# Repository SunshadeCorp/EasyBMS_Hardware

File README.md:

# EasyBMS_Hardware
PCB of the EasyBMS as an EAGLE project

Used EAGLE default design rules with one modification: under "Masks" in DRC settings, set "Limit" to 20mil to cover vias that have smaller drill size with solder mask.

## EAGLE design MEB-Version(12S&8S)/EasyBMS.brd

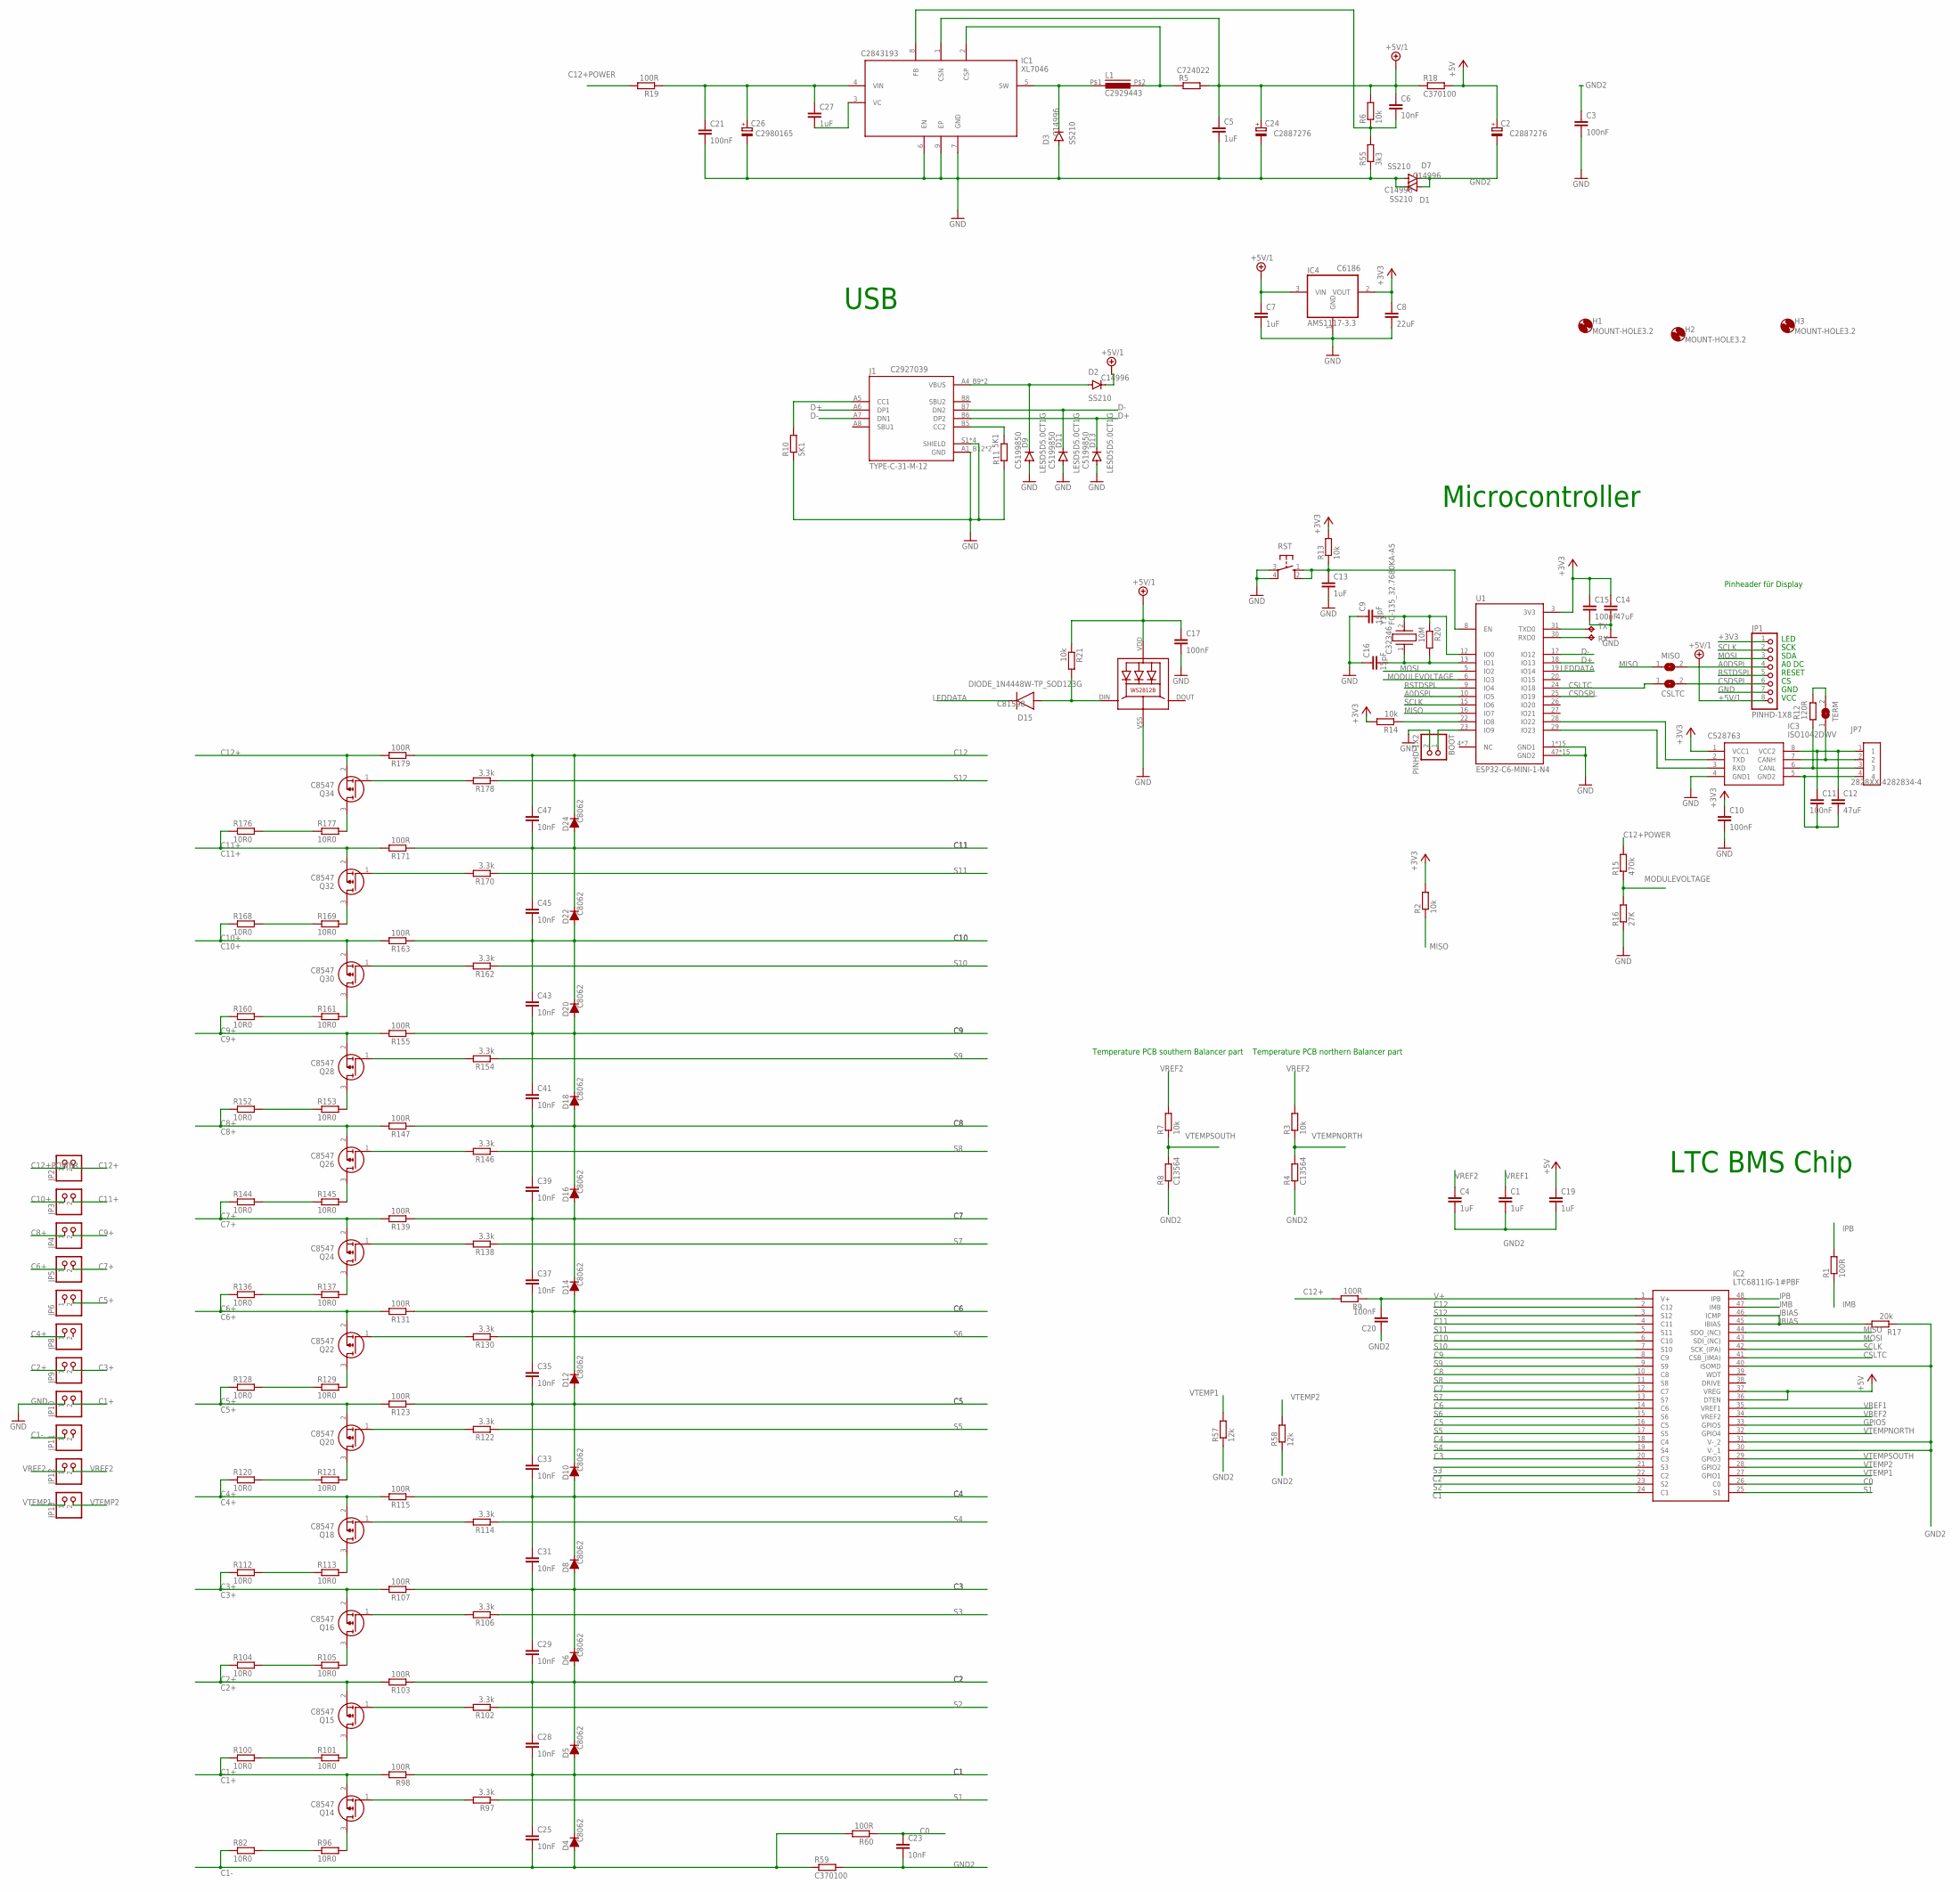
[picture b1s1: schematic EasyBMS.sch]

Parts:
BOOT: PINHD-1X2; 1X02
C1, C4, C5, C7, C13, C19: 1uF; C0402
C2, C24: CPOL-EU153CLV-0605; 153CLV-0605; LCSC C2887276
C3, C10, C11, C15, C17: 100nF; C0402
C6, C23, C25, C28, C29, C31, C33, C35, C37, C39, C41, C43, C45, C47: 10nF; C0402
C8: 22uF; C0603
C9, C16: 15pF; C0402
C12: 47uF; C1206
C14: 47uF; C0805
C20, C21: 100nF; C0805
C26: CPOL-EU153CLV-0605; 153CLV-0605; LCSC C2980165
C27: 1uF; C0603
CSLTC: SJ
D1, D2, D3, D7: SS210; DO214AC; LCSC C14996
D4, D5, D6, D8, D10, D12, D14, D16, D18, D20, D22, D24: D-FILL-MLL-34; MELF-MLL34; LCSC C8062
D9, D11, D13: LESD5D5.0CT1G; SOD523; LCSC C5199850
D15: DIODE_1N4448W-TP_SOD123G; SOD3715X135; LCSC C81598
H1, H2, H3: MOUNT-HOLE3.2; 3,2
IC1: XL7046; SOIC127P600X170-9N; LCSC C2843193
IC2: LTC6811IG-1#PBF; SOP50P780X200-48N
IC3: ISO1042DWV; SOIC127P1150X280-8N; LCSC C528763
IC4: AMS1117-3.3; SOT223; LCSC C6186
J1: TYPE-C-31-M-12; HRO_TYPE-C-31-M-12; LCSC C2927039
JP1: PINHD-1X8; 1X08
JP2, JP3, JP4, JP5, JP6, JP8, JP9, JP10, JP11, JP12, JP13: PINHD-1X2; 1X02; LCSC C3337950
JP7: 2828XX-4282834-4; TERMBLK_254-4N
L1: C2929443; CY75-100UH; LCSC C2929443
LED2: XL-1615RGBC-WS2812B
MISO: SJ
Q14, Q15, Q16, Q18, Q20, Q22, Q24, Q26, Q28, Q30, Q32, Q34: C8547; PG-SOT-23
R1: 100R; R0603
R2, R6, R13, R14, R21: 10k; R0402
R3, R7: 10k; R0603
R4, R8: C13564; R0603
R5: R-EU_R0402; R0402; LCSC C724022
R9, R60, R98, R103, R107, R115, R123, R131, R139, R147, R155, R163, R171, R179: 100R; R0402
R10, R11: 5K1; R0402
R12: 120R; R0402
R15: 470k; R0603
R16: 27K; R0603
R17: 20k; R0603
R18, R59: C370100; R1206
R19: 100R; R1206
R20: 10M; R0402
R55: 3k3; R0402
R57, R58: 12k; R0402
R82, R96, R100, R101, R104, R105, R112, R113, R120, R121, R128, R129, R136, R137, R144, R145, R152, R153, R160, R161, R168, R169, R176, R177: 10R0; R1206
R97, R102, R106, R114, R122, R130, R138, R146, R154, R162, R170, R178: 3.3k; R0402
RST: 10-XX; B3F-10XX
RX: TPB2,54; B2,54
TERM: SJ
TX: TPB2,54; B2,54
U1: ESP32-C6-MINI-1-N4; XCVR_ESP32-C6-MINI-1-N4; LCSC C5736265
Y1: FC-135_32.7680KA-A5; FC135327680KAA5; LCSC C32346

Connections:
+3V3: C8.1, C10.1, C14.1, C15.1, IC3.1 (VCC1), IC4.2 (VOUT), JP1.1, R2.2, R13.2, R14.2, U1.3 (3V3)
+5V: C2.+, C19.1, IC2.36 (DTEN), IC2.37 (VREG), R18.2
+5V/1: C5.1, C6.1, C7.1, C17.1, C24.+, D2.C, IC1.1 (CSN), IC4.3 (VIN), JP1.8, LED2.VDD, R5.2, R6.2, R18.1, R21.1
A0DSPL: JP1.4, MISO.2, U1.10 (IO5)
C0: C23.1, IC2.26 (C0), R60.1
C1: C25.1, C28.2, D4.1 (C), D5.2 (A), IC2.24 (C1), R98.1
C1+: JP10.2, Q14.2 (S), R98.2, R100.1
C1-: C25.2, D4.2 (A), JP11.1, R59.1, R60.2, R82.1
C2: C28.1, C29.2, D5.1 (C), D6.2 (A), IC2.22 (C2), R103.1
C2+: JP9.1, Q15.2 (S), R103.2, R104.1
C3: C29.1, C31.2, D6.1 (C), D8.2 (A), IC2.20 (C3), R107.1
C3+: JP9.2, Q16.2 (S), R107.2, R112.1
C4: C31.1, C33.2, D8.1 (C), D10.2 (A), IC2.18 (C4), R115.1
C4+: JP8.1, Q18.2 (S), R115.2, R120.1
C5: C33.1, C35.2, D10.1 (C), D12.2 (A), IC2.16 (C5), R123.1
C5+: JP6.2, Q20.2 (S), R123.2, R128.1
C6: C35.1, C37.2, D12.1 (C), D14.2 (A), IC2.14 (C6), R131.1
C6+: JP5.1, Q22.2 (S), R131.2, R136.1
C7: C37.1, C39.2, D14.1 (C), D16.2 (A), IC2.12 (C7), R139.1
C7+: JP5.2, Q24.2 (S), R139.2, R144.1
C8: C39.1, C41.2, D16.1 (C), D18.2 (A), IC2.10 (C8), R147.1
C8+: JP4.1, Q26.2 (S), R147.2, R152.1
C9: C41.1, C43.2, D18.1 (C), D20.2 (A), IC2.8 (C9), R155.1
C9+: JP4.2, Q28.2 (S), R155.2, R160.1
C10: C43.1, C45.2, D20.1 (C), D22.2 (A), IC2.6 (C10), R163.1
C10+: JP3.1, Q30.2 (S), R163.2, R168.1
C11: C45.1, C47.2, D22.1 (C), D24.2 (A), IC2.4 (C11), R171.1
C11+: JP3.2, Q32.2 (S), R171.2, R176.1
C12: C47.1, D24.1 (C), IC2.2 (C12), R179.1
C12+: JP2.2, Q34.2 (S), R9.2, R179.2
C12+POWER: JP2.1, R15.2, R19.2
CSDSPL: CSLTC.2, JP1.6, U1.25 (IO19)
CSLTC: CSLTC.1, IC2.41 (CSB_(IMA)), U1.24 (IO18)
D+: D13.C, J1.A6 (DP1), J1.B6 (DP2), U1.18 (IO13)
D-: D11.C, J1.A7 (DN1), J1.B7 (DN2), U1.17 (IO12)
GND: BOOT.2, C3.2, C5.2, C7.2, C8.2, C9.1, C10.2, C13.2, C14.2, C15.2, C16.1, C17.2, C21.2, C24.-, C26.-, D1.C, D3.A, D7.A, D9.A, D11.A, D13.A, IC1.6 (EN), IC1.7 (GND), IC1.9 (EP), IC3.4 (GND1), IC4.1 (GND), J1.A1_B12 (GND), J1.B1_A12 (GND), J1.S1 (SHIELD), J1.S2 (SHIELD), J1.S3 (SHIELD), J1.S4 (SHIELD), JP1.7, JP10.1, LED2.VSS (GND), R10.1, R11.1, R16.1, R55.1, RST.3, RST.4 (P1), U1.1 (GND1), U1.2 (GND1), U1.11 (GND1), U1.14 (GND1), U1.36 (GND1), U1.37 (GND1), U1.38 (GND1), U1.39 (GND1), U1.40 (GND1), U1.41 (GND1), U1.42 (GND1), U1.43 (GND1), U1.44 (GND1), U1.45 (GND1), U1.46 (GND1), U1.47 (GND2), U1.48 (GND2), U1.49_1 (GND2), U1.49_2 (GND2), U1.49_3 (GND2), U1.49_4 (GND2), U1.49_5 (GND2), U1.49_6 (GND2), U1.49_7 (GND2), U1.49_8 (GND2), U1.49_9 (GND2), U1.50 (GND2), U1.51 (GND2), U1.52 (GND2), U1.53 (GND2)
GND2: C1.2, C2.-, C3.1, C4.2, C19.2, C20.1, C23.2, D1.A, D7.C, IC2.30 (V-_1), IC2.31 (V-_2), IC2.40 (ISOMD), R4.1, R8.1, R17.1, R57.1, R58.1, R59.2
GPIO5: IC2.33 (GPIO5)
IBIAS: IC2.45 (IBIAS), IC2.46 (ICMP), R17.2
IMB: IC2.47 (IMB), R1.1
IPB: IC2.48 (IPB), R1.2
LEDDATA: D15.1 (C), U1.19 (IO14)
MISO: IC2.44 (SDO_(NC)), MISO.1, R2.1, U1.16 (IO7)
MODULEVOLTAGE: R15.1, R16.2, U1.6 (IO3)
MOSI: IC2.43 (SDI_(NC)), JP1.3, U1.5 (IO2)
unnamed: IC3.2 (TXD), U1.28 (IO22)
unnamed: TX.TP, U1.31 (TXD0)
unnamed: D2.A, D9.C, J1.A4_B9 (VBUS), J1.B4_A9 (VBUS)
unnamed: C27.2, IC1.3 (VC)
unnamed: D3.C, IC1.5 (SW), L1.P$1 (1)
unnamed: J1.A5 (CC1), R10.2
unnamed: J1.B5 (CC2), R11.2
unnamed: RX.TP, U1.30 (RXD0)
unnamed: IC3.3 (RXD), U1.29 (IO23)
unnamed: C11.1, C12.1, IC3.8 (VCC2), JP7.1
unnamed: IC3.7 (CANH), JP7.2, TERM.1
unnamed: IC3.6 (CANL), JP7.3, R12.1
unnamed: IC1.2 (CSP), L1.P$2 (2), R5.1
unnamed: C11.2, C12.2, IC3.5 (GND2), JP7.4
unnamed: C13.1, R13.1, RST.1 (S), RST.2 (S1), U1.8 (EN)
unnamed: R82.2, R96.1
unnamed: R12.2, TERM.2
unnamed: R14.1, U1.22 (IO8)
unnamed: BOOT.1, U1.23 (IO9)
unnamed: C9.2, R20.1, U1.12 (IO0), Y1.2
unnamed: C16.2, R20.2, U1.13 (IO1), Y1.1
unnamed: D15.2 (A), LED2.DIN (DI), R21.2
unnamed: C6.2, IC1.8 (FB), R6.1, R55.2
unnamed: C21.1, C26.+, C27.1, IC1.4 (VIN), R19.1
unnamed: Q14.3 (D), R96.2
unnamed: Q14.1 (G), R97.2
unnamed: R100.2, R101.1
unnamed: Q15.3 (D), R101.2
unnamed: Q15.1 (G), R102.2
unnamed: R104.2, R105.1
unnamed: Q16.3 (D), R105.2
unnamed: Q16.1 (G), R106.2
unnamed: R112.2, R113.1
unnamed: Q18.3 (D), R113.2
unnamed: Q18.1 (G), R114.2
unnamed: R120.2, R121.1
unnamed: Q20.3 (D), R121.2
unnamed: Q20.1 (G), R122.2
unnamed: R128.2, R129.1
unnamed: Q22.3 (D), R129.2
unnamed: Q22.1 (G), R130.2
unnamed: R136.2, R137.1
unnamed: Q24.3 (D), R137.2
unnamed: Q24.1 (G), R138.2
unnamed: R144.2, R145.1
unnamed: Q26.3 (D), R145.2
unnamed: Q26.1 (G), R146.2
unnamed: R152.2, R153.1
unnamed: Q28.3 (D), R153.2
unnamed: Q28.1 (G), R154.2
unnamed: R160.2, R161.1
unnamed: Q30.3 (D), R161.2
unnamed: Q30.1 (G), R162.2
unnamed: R168.2, R169.1
unnamed: Q32.3 (D), R169.2
unnamed: Q32.1 (G), R170.2
unnamed: R176.2, R177.1
unnamed: Q34.3 (D), R177.2
unnamed: Q34.1 (G), R178.2
RSTDSPL: JP1.5, U1.9 (IO4)
S1: IC2.25 (S1), R97.1
S2: IC2.23 (S2), R102.1
S3: IC2.21 (S3), R106.1
S4: IC2.19 (S4), R114.1
S5: IC2.17 (S5), R122.1
S6: IC2.15 (S6), R130.1
S7: IC2.13 (S7), R138.1
S8: IC2.11 (S8), R146.1
S9: IC2.9 (S9), R154.1
S10: IC2.7 (S10), R162.1
S11: IC2.5 (S11), R170.1
S12: IC2.3 (S12), R178.1
SCLK: IC2.42 (SCK_(IPA)), JP1.2, U1.15 (IO6)
V+: C20.2, IC2.1 (V+), R9.1
VREF1: C1.1, IC2.35 (VREF1)
VREF2: C4.1, IC2.34 (VREF2), JP12.1, JP12.2, R3.2, R7.2
VTEMP1: IC2.27 (GPIO1), JP13.1, R57.2
VTEMP2: IC2.28 (GPIO2), JP13.2, R58.2
VTEMPNORTH: IC2.32 (GPIO4), R3.1, R4.2
VTEMPSOUTH: IC2.29 (GPIO3), R7.1, R8.2

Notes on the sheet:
LED
SCK
SDA
A0 DC
RESET
GND
VCC
Pinheader für Display
Microcontroller
LTC BMS Chip
Temperature PCB northern Balancer part
Temperature PCB southern Balancer part
USB

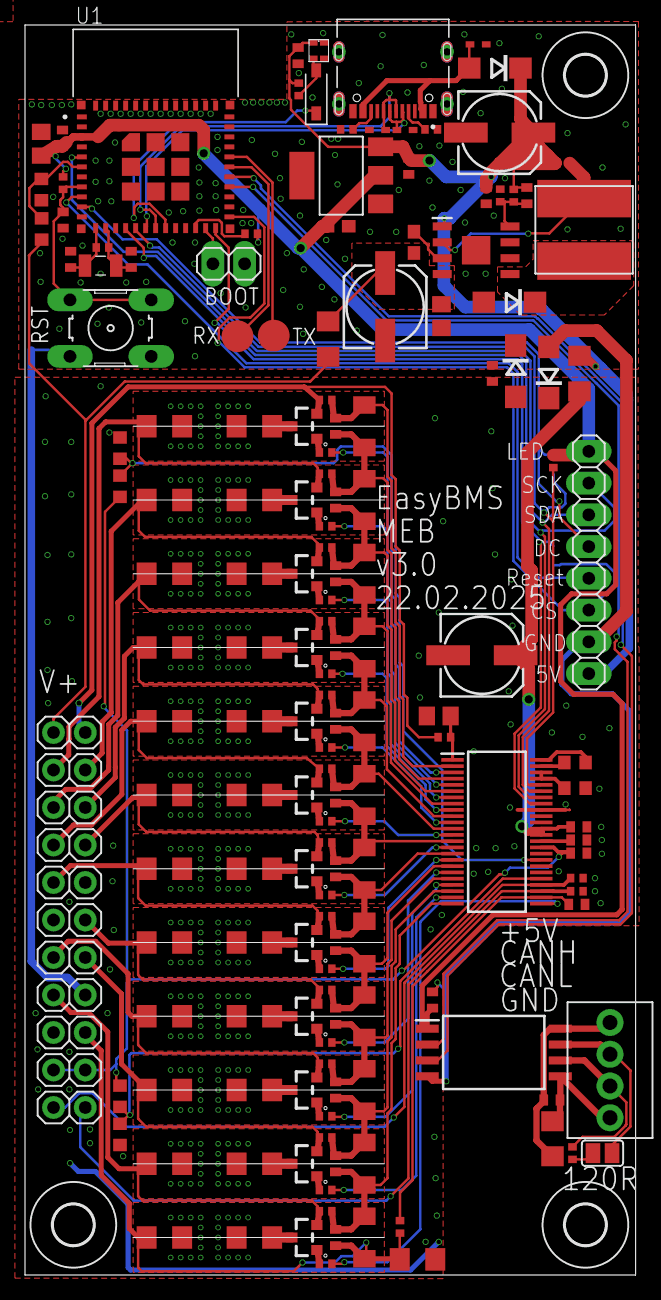
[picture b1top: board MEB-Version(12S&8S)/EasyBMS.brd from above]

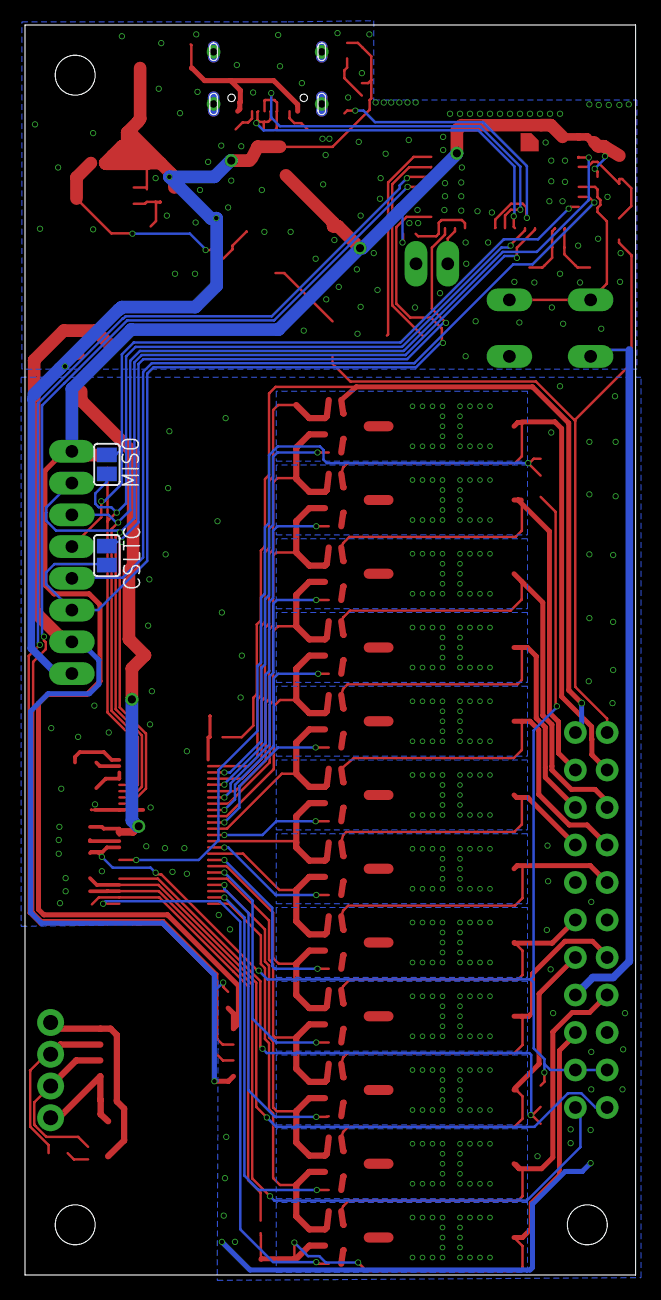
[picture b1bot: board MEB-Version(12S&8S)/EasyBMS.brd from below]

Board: 2 copper layers, 48.9 x 100.0 mm, 174 parts (2 on the bottom side), 124 nets.

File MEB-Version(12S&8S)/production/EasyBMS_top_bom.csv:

Comment,Designator,Footprint,LCSC Part #
1uF,C2 C24 C26 D4 D5 D6 D8 D10 D12 D14 D16 D18 D20 D22 D24 R5 TERM C1 C4 C5 C7 C13 C19,C0402,
1uF,C27,C0603,
3.3k,R97 R102 R106 R114 R122 R130 R138 R146 R154 R162 R170 R178,R0402,
3k3,R55,R0402,
5K1,R10 R11,R0402,
10M,R20,R0402,
10R0,R82 R96 R100 R101 R104 R105 R112 R113 R120 R121 R128 R129 R136 R137 R144 R145 R152 R153 R160 R161 R168 R169 R176 R177,R1206,
10k,R2,R0402,
10k,R3,R0603,
10k,R6,R0402,
10k,R7,R0603,
10k,R13 R14 R21,R0402,
10nF,C6 C23 C25 C28 C29 C31 C33 C35 C37 C39 C41 C43 C45 C47,C0402,
12k,R57 R58,R0402,
15pF,C9 C16,C0402,
20k,R17,R0603,
22uF,C8,C0603,
27K,R16,R0402,
47µF,C12,C1206,
47µF,C14,C0805,
100R,R1,R0603,
100R,R9,R0402,
100R,R19,R1206,
100R,R60 R98 R103 R107 R115 R123 R131 R139 R147 R155 R163 R171 R179,R0402,
100nF,C3 C10 C11 C15 C17,C0402,
100nF,C20 C21,C0805,
120R,R12,R0402,
470k,R15,R0402,
AMS1117-3.3,IC4,SOT223,C6186
C8547,Q14 Q15 Q16 Q18 Q20 Q22 Q24 Q26 Q28 Q30 Q32 Q34,PG-SOT-23,
C13564,R4 R8,R0603,
C370100,R18 R59,R1206,
C2929443,L1,CY75-100UH,C2929443
DIODE_1N4448W-TP_SOD123G,D15,SOD3715X135,C81598
ESP32-C6-MINI-1-N4,U1,XCVR_ESP32-C6-MINI-1-N4,C5736265
FC-135_32.7680KA-A5,Y1,FC135327680KAA5,C32346
ISO1042DWV,IC3,SOIC127P1150X280-8N,C528763
LESD5D5.0CT1G,D9 D11 D13,SOD523,C5199850
LTC6811IG-1#PBF,IC2,SOP50P780X200-48N,
SS210,D1 D2 D3 D7,DO214AC,C14996
TPB2 54,RX,B2 54,
TPB2 54,TX,B2 54,
TYPE-C-31-M-12,J1,HRO_TYPE-C-31-M-12,C2927039
XL-1615RGBC-WS2812B,LED2,XL-1615RGBC-WS2812B,C5349954
XL7046,IC1,SOIC127P600X170-9N,C2843193

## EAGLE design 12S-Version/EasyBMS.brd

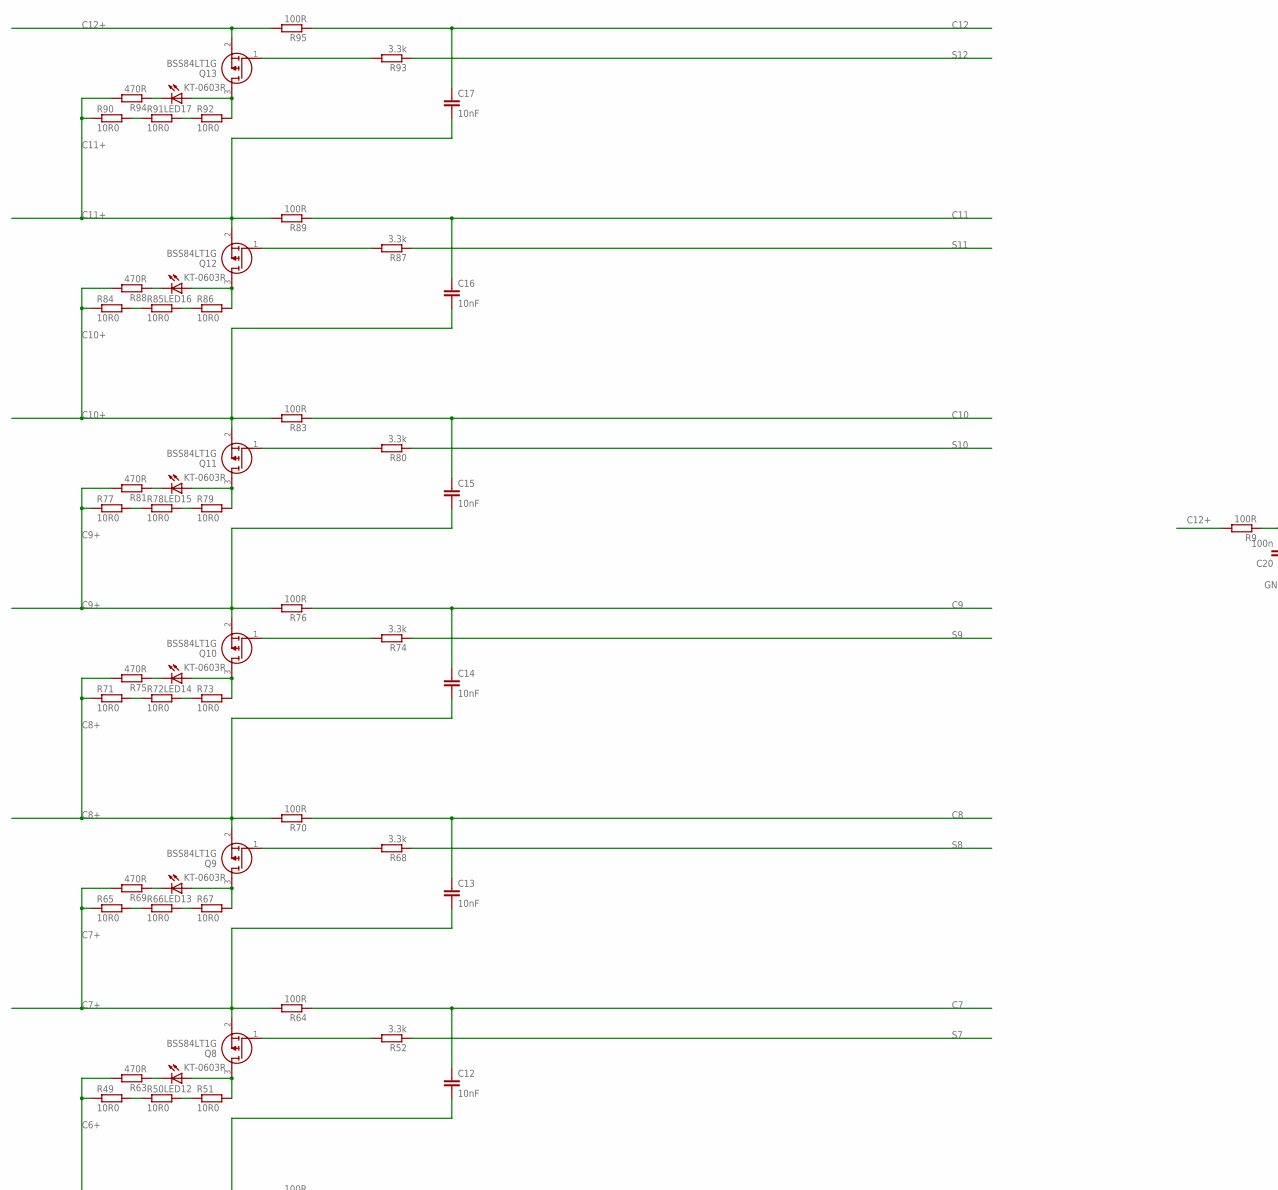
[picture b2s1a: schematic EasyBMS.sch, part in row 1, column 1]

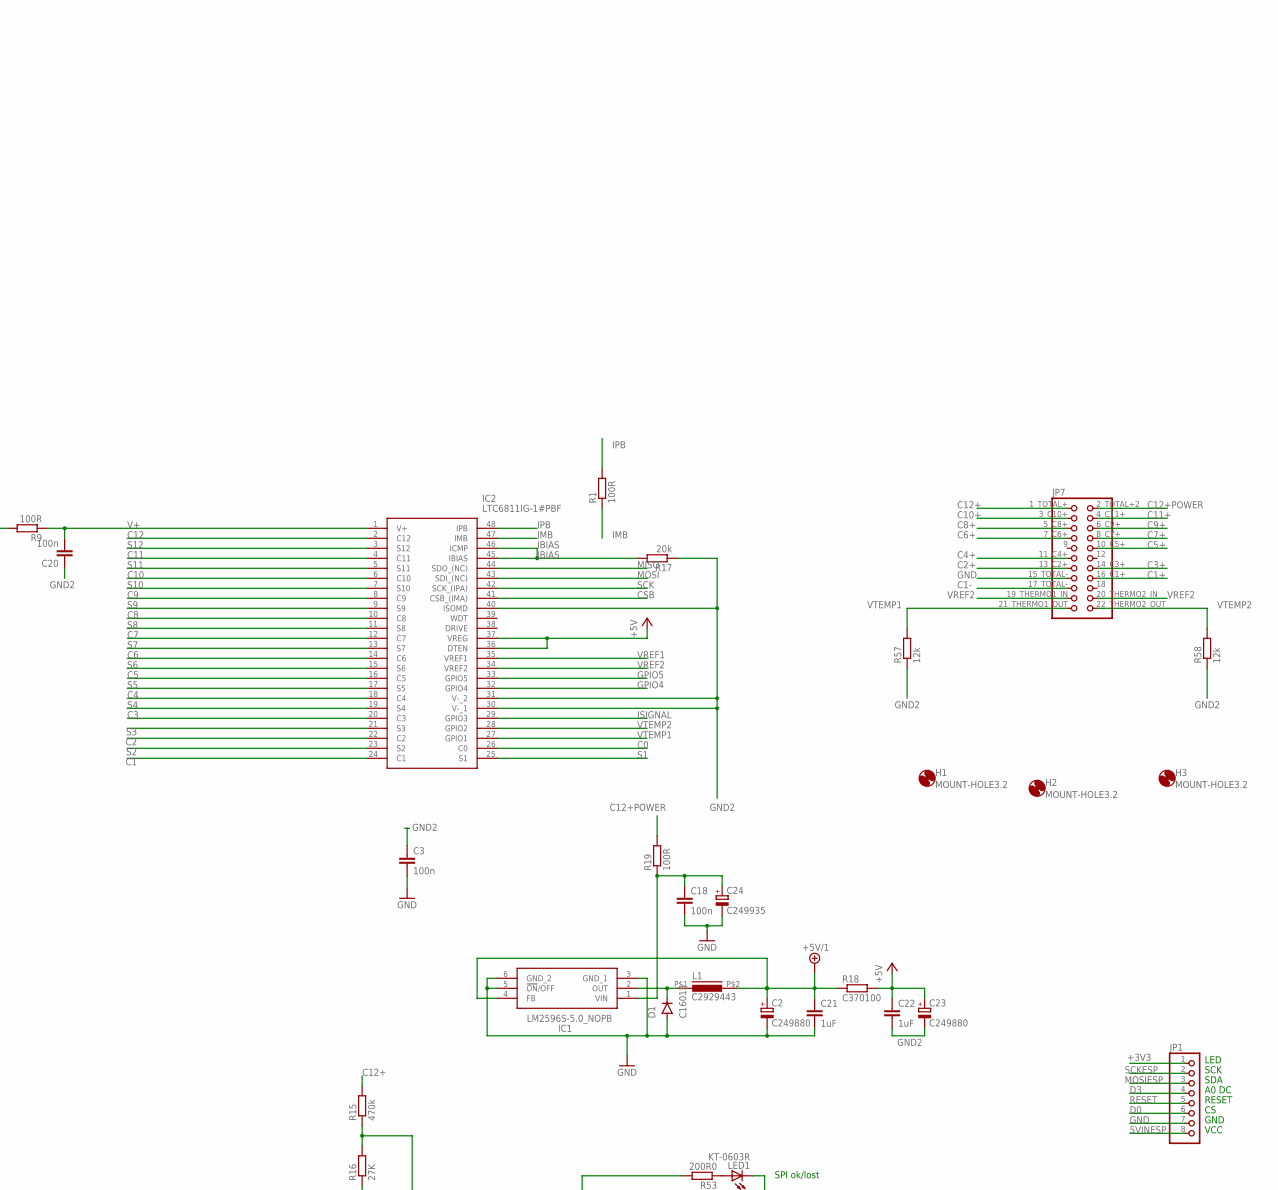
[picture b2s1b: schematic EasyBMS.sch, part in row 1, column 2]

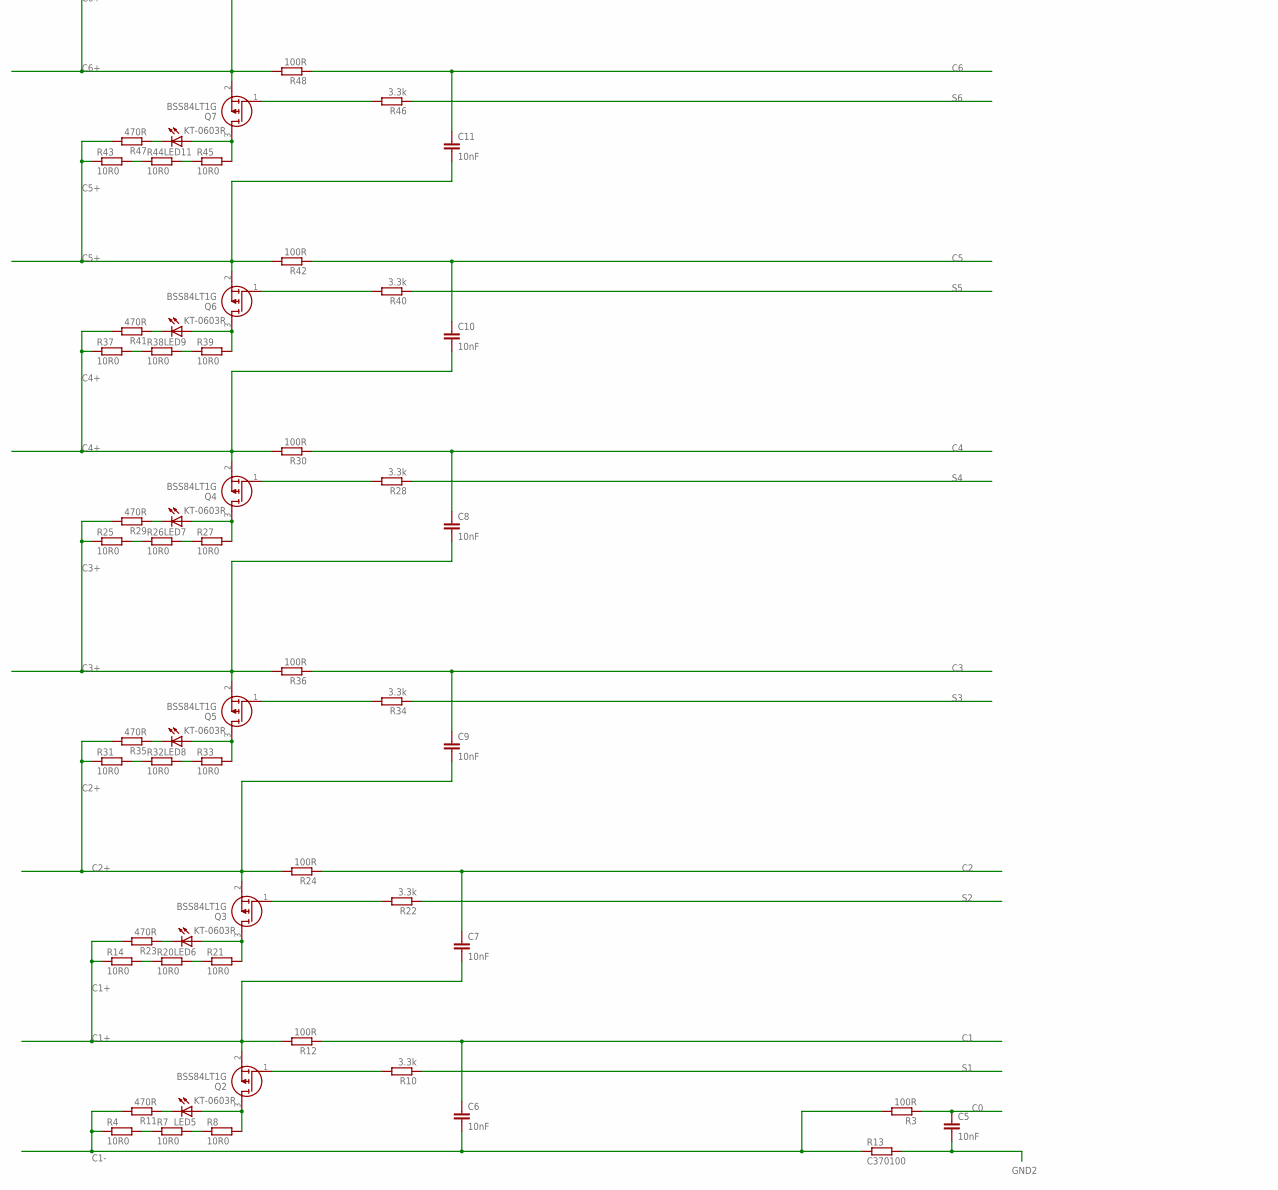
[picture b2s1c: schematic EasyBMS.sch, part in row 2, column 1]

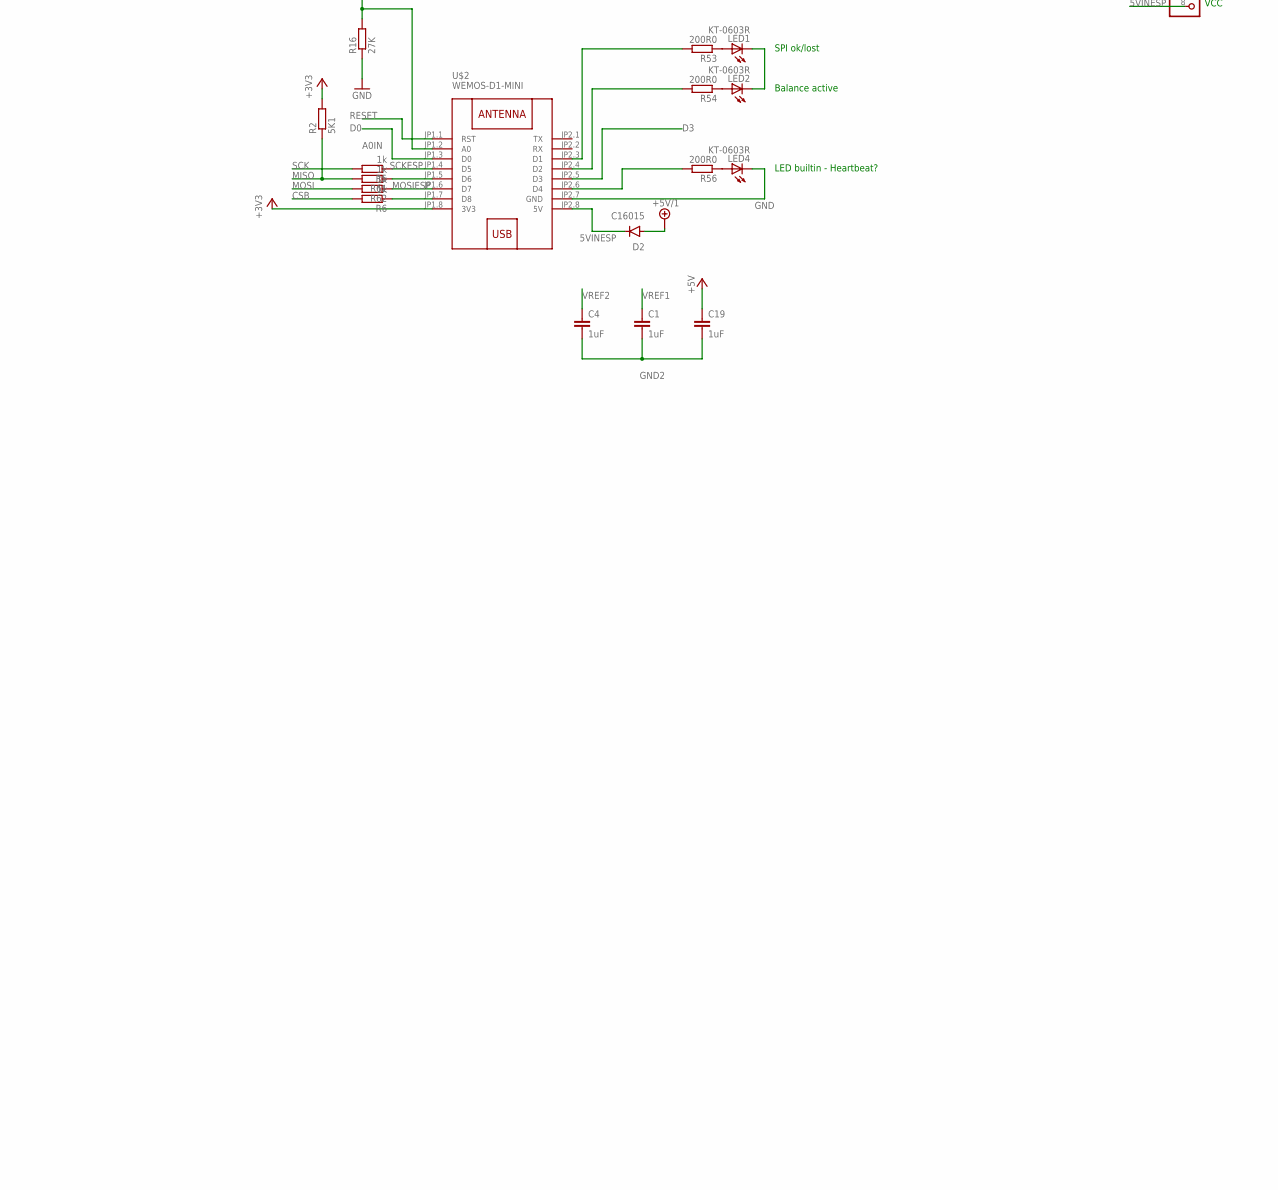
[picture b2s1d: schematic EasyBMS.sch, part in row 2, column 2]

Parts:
C1, C4, C19, C21, C22: 1uF; C1206
C2, C23: C249880; UD-8X10_NICHICON
C3, C18, C20: 100n; C0402
C5, C6, C7, C8, C9, C10, C11, C12, C13, C14, C15, C16, C17: 10nF; C0402
C24: C249935; WCAP-ASLI_16X17(DXL)
D1, D2: C16015; DO214AC
H1, H2, H3: MOUNT-HOLE3.2; 3,2
IC1: LM2596S-5.0_NOPB; KTT0005B
IC2: LTC6811IG-1#PBF; SOP50P780X200-48N
JP1: PINHD-1X8; 1X08
JP7: PINHD-2X11_MEB12S; 2X11_MEB12S
L1: C2929443; CY75-100UH
LED1, LED2, LED4, LED5, LED6, LED7, LED8, LED9, LED11, LED12, LED13, LED14, LED15, LED16, LED17: KT-0603R; CHIPLED_0603
Q2, Q3, Q4, Q5, Q6, Q7, Q8, Q9, Q10, Q11, Q12, Q13: BSS84LT1G; SOT96P237X111-3N
R1: 100R; R0603
R2: 5K1; R0603
R3, R9, R12, R24, R30, R36, R42, R48, R64, R70, R76, R83, R89, R95: 100R; R0402
R4, R7, R8, R14, R20, R21, R25, R26, R27, R31, R32, R33, R37, R38, R39, R43, R44, R45, R49, R50, R51, R65, R66, R67, R71, R72, R73, R77, R78, R79, R84, R85, R86, R90, R91, R92: 10R0; R1206
R5, R6, R61, R62: 1k; R0603
R10, R22, R28, R34, R40, R46, R52, R68, R74, R80, R87, R93: 3.3k; R0402
R11, R23, R29, R35, R41, R47, R63, R69, R75, R81, R88, R94: 470R; R0402
R13, R18: C370100; R1206
R15: 470k; R0603
R16: 27K; R0603
R17: 20k; R0603
R19: 100R; R1206
R53, R54, R56: 200R0; R0603
R57, R58: 12k; R0603
U$2: WEMOS-D1-MINI

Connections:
5VINESP: D2.C, JP1.8, U$2.JP2.8 (5V); also elsewhere on the board
+3V3: JP1.1, R2.2, U$2.JP1.8 (3V3); also elsewhere on the board
+5V: C19.1, C22.1, C23.+, IC2.36 (DTEN), IC2.37 (VREG), R18.2
+5V/1: C2.+, C21.1, D2.A, IC1.4 (FB), L1.P$2 (2), R18.1
A0IN: R15.1, R16.2, U$2.JP1.2 (A0)
C0: C5.1, IC2.26 (C0), R3.1
C1: C6.1, IC2.24 (C1), R12.1
C1+: C7.2, JP7.16_C1+, Q2.2 (S), R12.2, R14.1, R23.2
C1-: C6.2, JP7.17_TOTAL- (TOTAL-), R3.2, R4.1, R11.2, R13.1
C2: C7.1, IC2.22 (C2), R24.1
C2+: C9.2, JP7.13_C2+, Q3.2 (S), R24.2, R31.1, R35.2
C3: C9.1, IC2.20 (C3), R36.1
C3+: C8.2, JP7.14_C3+, Q5.2 (S), R25.1, R29.2, R36.2
C4: C8.1, IC2.18 (C4), R30.1
C4+: C10.2, JP7.11_C4+, Q4.2 (S), R30.2, R37.1, R41.2
C5: C10.1, IC2.16 (C5), R42.1
C5+: C11.2, JP7.10_C5+, Q6.2 (S), R42.2, R43.1, R47.2
C6: C11.1, IC2.14 (C6), R48.1
C6+: C12.2, JP7.7_C6+, Q7.2 (S), R48.2, R49.1, R63.2
C7: C12.1, IC2.12 (C7), R64.1
C7+: C13.2, JP7.8_C7+, Q8.2 (S), R64.2, R65.1, R69.2
C8: C13.1, IC2.10 (C8), R70.1
C8+: C14.2, JP7.5_C8+, Q9.2 (S), R70.2, R71.1, R75.2
C9: C14.1, IC2.8 (C9), R76.1
C9+: C15.2, JP7.6_C9+, Q10.2 (S), R76.2, R77.1, R81.2
C10: C15.1, IC2.6 (C10), R83.1
C10+: C16.2, JP7.3_C10+, Q11.2 (S), R83.2, R84.1, R88.2
C11: C16.1, IC2.4 (C11), R89.1
C11+: C17.2, JP7.4_C11+, Q12.2 (S), R89.2, R90.1, R94.2
C12: C17.1, IC2.2 (C12), R95.1
C12+: JP7.1_TOTAL+, Q13.2 (S), R9.2, R15.2, R95.2
C12+POWER: JP7.2_TOTAL+2 (2_CTOTAL+), R19.2
CSB: IC2.41 (CSB_(IMA)), R6.2
D0: JP1.6, U$2.JP1.3 (D0)
D3: JP1.4, U$2.JP2.5 (D3)
GND: C2.-, C3.2, C18.2, C21.2, C24.2 (-), D1.A, IC1.3 (GND_1), IC1.5 (!ON!/OFF), IC1.6 (GND_2), JP1.7, JP7.15_TOTAL-, LED4.C, R16.1, U$2.JP2.7 (GND)
GND2: C1.2, C3.1, C4.2, C5.2, C19.2, C20.1, C22.2, C23.-, IC2.30 (V-_1), IC2.31 (V-_2), IC2.40 (ISOMD), R13.2, R17.1, R57.1, R58.1
GPIO4: IC2.32 (GPIO4)
GPIO5: IC2.33 (GPIO5)
IBIAS: IC2.45 (IBIAS), IC2.46 (ICMP), R17.2
IMB: IC2.47 (IMB), R1.1
IPB: IC2.48 (IPB), R1.2
ISIGNAL: IC2.29 (GPIO3)
MISO: IC2.44 (SDO_(NC)), R2.1, R61.2
unnamed: LED1.A, R53.1
unnamed: LED2.A, R54.1
unnamed: LED1.C, LED2.C
unnamed: LED4.A, R56.1
unnamed: R4.2, R7.1
unnamed: R7.2, R8.1
unnamed: LED5.A, Q2.3 (D), R8.2
unnamed: Q2.1 (G), R10.2
unnamed: LED5.C, R11.1
unnamed: R14.2, R20.1
unnamed: R20.2, R21.1
unnamed: R6.1, U$2.JP1.7 (D8)
unnamed: LED6.A, Q3.3 (D), R21.2
unnamed: D1.C, IC1.2 (OUT), L1.P$1 (1)
unnamed: Q3.1 (G), R22.2
unnamed: LED6.C, R23.1
unnamed: R25.2, R26.1
unnamed: R26.2, R27.1
unnamed: LED7.A, Q4.3 (D), R27.2
unnamed: Q4.1 (G), R28.2
unnamed: LED7.C, R29.1
unnamed: R31.2, R32.1
unnamed: R32.2, R33.1
unnamed: LED8.A, Q5.3 (D), R33.2
unnamed: R56.2, U$2.JP2.6 (D4)
unnamed: Q5.1 (G), R34.2
unnamed: LED8.C, R35.1
unnamed: R37.2, R38.1
unnamed: R38.2, R39.1
unnamed: LED9.A, Q6.3 (D), R39.2
unnamed: Q6.1 (G), R40.2
unnamed: LED9.C, R41.1
unnamed: R43.2, R44.1
unnamed: R44.2, R45.1
unnamed: LED11.A, Q7.3 (D), R45.2
unnamed: Q7.1 (G), R46.2
unnamed: LED11.C, R47.1
unnamed: R49.2, R50.1
unnamed: R50.2, R51.1
unnamed: LED12.A, Q8.3 (D), R51.2
unnamed: Q8.1 (G), R52.2
unnamed: LED12.C, R63.1
unnamed: R65.2, R66.1
unnamed: R66.2, R67.1
unnamed: LED13.A, Q9.3 (D), R67.2
unnamed: Q9.1 (G), R68.2
unnamed: LED13.C, R69.1
unnamed: R71.2, R72.1
unnamed: R72.2, R73.1
unnamed: LED14.A, Q10.3 (D), R73.2
unnamed: Q10.1 (G), R74.2
unnamed: LED14.C, R75.1
unnamed: R77.2, R78.1
unnamed: R78.2, R79.1
unnamed: LED15.A, Q11.3 (D), R79.2
unnamed: Q11.1 (G), R80.2
unnamed: LED15.C, R81.1
unnamed: R84.2, R85.1
unnamed: R85.2, R86.1
unnamed: LED16.A, Q12.3 (D), R86.2
unnamed: Q12.1 (G), R87.2
unnamed: LED16.C, R88.1
unnamed: R90.2, R91.1
unnamed: R91.2, R92.1
unnamed: R53.2, U$2.JP2.3 (D1)
unnamed: LED17.A, Q13.3 (D), R92.2
unnamed: Q13.1 (G), R93.2
unnamed: R61.1, U$2.JP1.5 (D6)
unnamed: LED17.C, R94.1
unnamed: C18.1, C24.1 (+), IC1.1 (VIN), R19.1
unnamed: R54.2, U$2.JP2.4 (D2)
RESET: JP1.5, U$2.JP1.1 (RST)
S1: IC2.25 (S1), R10.1
S2: IC2.23 (S2), R22.1
S3: IC2.21 (S3), R34.1
S4: IC2.19 (S4), R28.1
S5: IC2.17 (S5), R40.1
S6: IC2.15 (S6), R46.1
S7: IC2.13 (S7), R52.1
S8: IC2.11 (S8), R68.1
S9: IC2.9 (S9), R74.1
S10: IC2.7 (S10), R80.1
S11: IC2.5 (S11), R87.1
S12: IC2.3 (S12), R93.1
V+: C20.2, IC2.1 (V+), R9.1
VREF1: C1.1, IC2.35 (VREF1)
VREF2: C4.1, IC2.34 (VREF2), JP7.19_THERMO1_IN, JP7.20_THERMO2_IN
VTEMP1: IC2.27 (GPIO1), JP7.21_THERMO1_OUT, R57.2
VTEMP2: IC2.28 (GPIO2), JP7.22_THERMO2_OUT, R58.2

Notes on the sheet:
SPI ok/lost
Balance active
LED builtin - Heartbeat?
LED
SCK
SDA
A0 DC
RESET
GND
VCC

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

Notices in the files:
parts and their libraries:
diy-modules: Released under the Creative Commons Attribution 4.0 International License: http://creativecommons.org/licenses/by/4.0
